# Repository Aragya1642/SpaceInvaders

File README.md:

# Space Invaders Bop-It

The Space Invaders Bop-It is an embedded interactive game that combines the reflex-based mechanics of Bop-It with the space-themed gameplay of Space Invaders. Built around the ATMega328P microcontroller, this project incorporates physical controls, audio/visual feedback, and a custom PCB to deliver an engaging and fast-paced user experience.

## Overview

Players are prompted with random commands such as:

- Turn Left
- Turn Right
- Throttle Up
- Shoot

Each command corresponds to one of the three physical inputs:
- Steering Wheel
- Throttle Lever
- Push Button

Correct responses increase the player’s score, flash a green LED, and play a "ding" sound. Incorrect or delayed responses trigger a red LED, a crash sound, and reset the game. The objective is to reach a score of 99 without failure.

## Features

- Three unique analog/digital inputs: steering, throttle, fire
- LCD screen to display real-time score
- DFPlayer Mini for audio feedback via speakers
- LED indicators for success and failure
- Finite State Machine logic with decreasing response time per successful input
- Enclosure design using Onshape CAD and laser-cut acrylic
- Custom PCB built in KiCad with support for power regulation, audio, and I/O

## Repository Structure

├── src/ # Arduino software

├── pcb/ # KiCad PCB design files

├── cad/ # CAD screenshots and Onshape link

├── docs/ # Final report and additional documentation

├── media/ # Photos and video demonstration

├── LICENSE

└── README.md

## How to Build

1. Clone this repository:
https://github.com/iamratedpg13/SpaceInvaders.git

2. Upload `src/main.ino` to an ATMega328P or Arduino Uno-compatible board.

3. Assemble the PCB using the files in the `pcb/` directory.

4. 3D print or laser cut enclosure parts using the files or images in `cad/`.

5. Copy required `.mp3` sound files to a FAT32-formatted microSD card and insert it into the DFPlayer Mini module.

6. Power the system using a regulated 5V supply (e.g., 9V battery with onboard regulator).

## Video Demo

Watch the game in action:  
https://www.youtube.com/watch?v=FF51uR-_Np4

## Key Implementation Notes

- The throttle and wheel are analog inputs (potentiometers); the button is digital.
- AVCC on the ATMega must be tied to 5V for proper ADC operation.
- Sound and display use UART and I2C, respectively; serial conflicts were resolved manually.
- Input drift was corrected in software by sampling baseline values at startup.

## Team Members

- PJ Granieri – Hardware and PCB Design
- Joshua Krymgold – Software Development
- Aragya Goyal – Enclosure Design and CAD

## License

This project is licensed under the MIT License. See the LICENSE file for details.

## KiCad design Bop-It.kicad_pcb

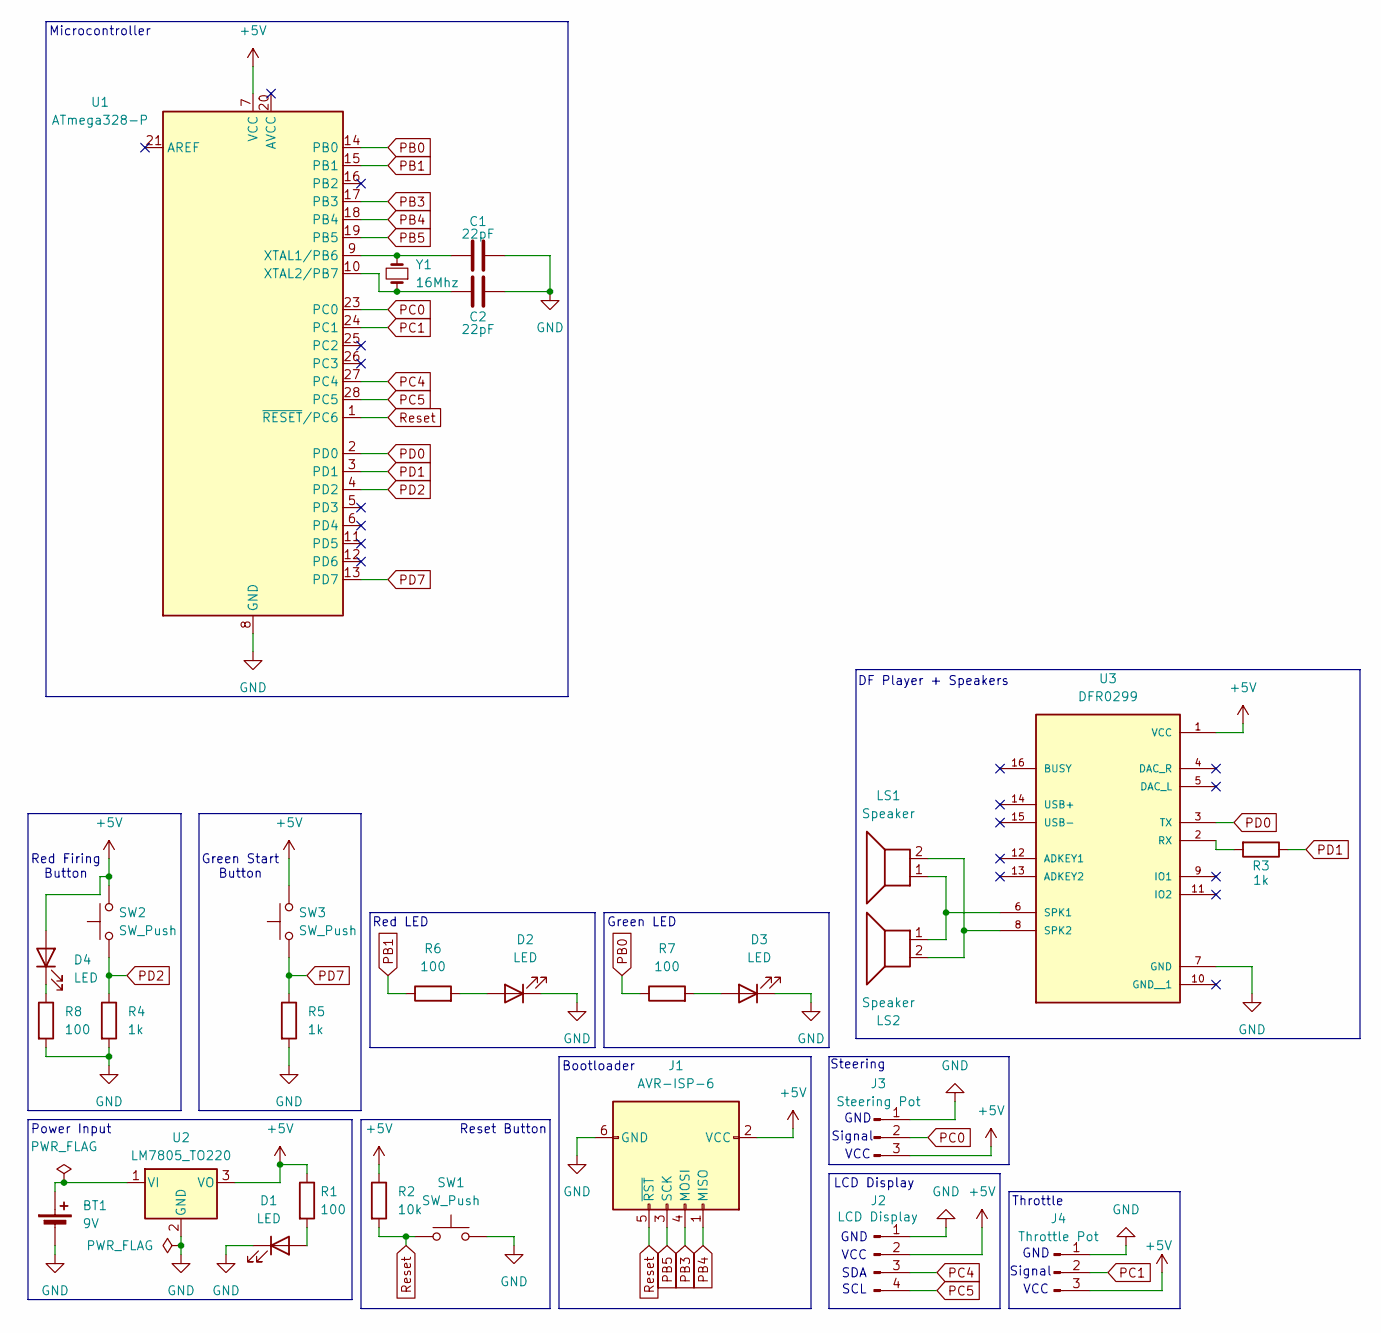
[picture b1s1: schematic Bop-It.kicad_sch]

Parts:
BT1: 9V; PinHeader_1x02_P2.54mm_Vertical
C1, C2: 22pF; C_Disc_D5.0mm_W2.5mm_P5.00mm
D1: LED; LED_D5.0mm
D2, D3, D4: LED; PinHeader_1x02_P2.54mm_Vertical
J1: AVR-ISP-6; PinHeader_2x03_P2.54mm_Vertical
J2: LCD Display; PinHeader_1x04_P2.54mm_Vertical
J3: Steering Pot; PinHeader_1x03_P2.54mm_Vertical
J4: Throttle Pot; PinHeader_1x03_P2.54mm_Vertical
LS1, LS2: Speaker; PinHeader_1x02_P2.54mm_Vertical
R1, R6, R7, R8: 100; R_Axial_DIN0207_L6.3mm_D2.5mm_P7.62mm_Horizontal
R2: 10k; R_Axial_DIN0207_L6.3mm_D2.5mm_P7.62mm_Horizontal
R3, R4, R5: 1k; R_Axial_DIN0207_L6.3mm_D2.5mm_P7.62mm_Horizontal
SW1: SW_Push; SW_PUSH-12mm
SW2, SW3: SW_Push; PinHeader_1x02_P2.54mm_Vertical
U1: ATmega328-P; DIP-28_W7.62mm
U2: LM7805_TO220; TO-220-3_Vertical
U3: DFR0299; MODULE_DFR0299
Y1: 16Mhz; XTAL_HC49P488W46L1150T500H350

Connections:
+5V: D4.2 (A), J1.2 (VCC), J2.2, J3.3, J4.3, R1.1, R2.1, SW2.2, SW3.2, U1.7 (VCC), U2.3 (VO), U3.1 (VCC)
GND: BT1.2 (-), C1.2, C2.2, D1.1 (K), D2.1 (K), D3.1 (K), J1.6 (GND), J2.1, J3.1, J4.1, R4.2, R5.2, R8.2, SW1.2, U1.8 (GND), U1.22 (GND), U2.2 (GND), U3.7 (GND)
unnamed: BT1.1 (+), U2.1 (VI)
unnamed: D1.2 (A), R1.2
unnamed: D2.2 (A), R6.2
unnamed: D3.2 (A), R7.2
unnamed: D4.1 (K), R8.1
unnamed: C1.1, U1.9 (XTAL1/PB6), Y1.2
unnamed: C2.1, U1.10 (XTAL2/PB7), Y1.1
unnamed: R3.2, U3.2 (RX)
unnamed: LS1.1, LS2.1, U3.6 (SPK1)
unnamed: LS1.2, LS2.2, U3.8 (SPK2)
PB0: R7.1, U1.14 (PB0)
PB1: R6.1, U1.15 (PB1)
PB3: J1.4 (MOSI), U1.17 (PB3)
PB4: J1.1 (MISO), U1.18 (PB4)
PB5: J1.3 (SCK), U1.19 (PB5)
PC0: J3.2, U1.23 (PC0)
PC1: J4.2, U1.24 (PC1)
PC4: J2.3, U1.27 (PC4)
PC5: J2.4, U1.28 (PC5)
PD0: U1.2 (PD0), U3.3 (TX)
PD1: R3.1, U1.3 (PD1)
PD2: R4.1, SW2.1, U1.4 (PD2)
PD7: R5.1, SW3.1, U1.13 (PD7)
Reset: J1.5 (~RST), R2.2, SW1.1, U1.1 (~RESET/PC6)

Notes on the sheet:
Steering
VCC
DF Player + Speakers
GND
SDA
Throttle
Signal
Red LED
Reset Button
Bootloader
Power Input
LCD Display
Green LED
SCL
Red Firing Button
Green Start Button
Microcontroller

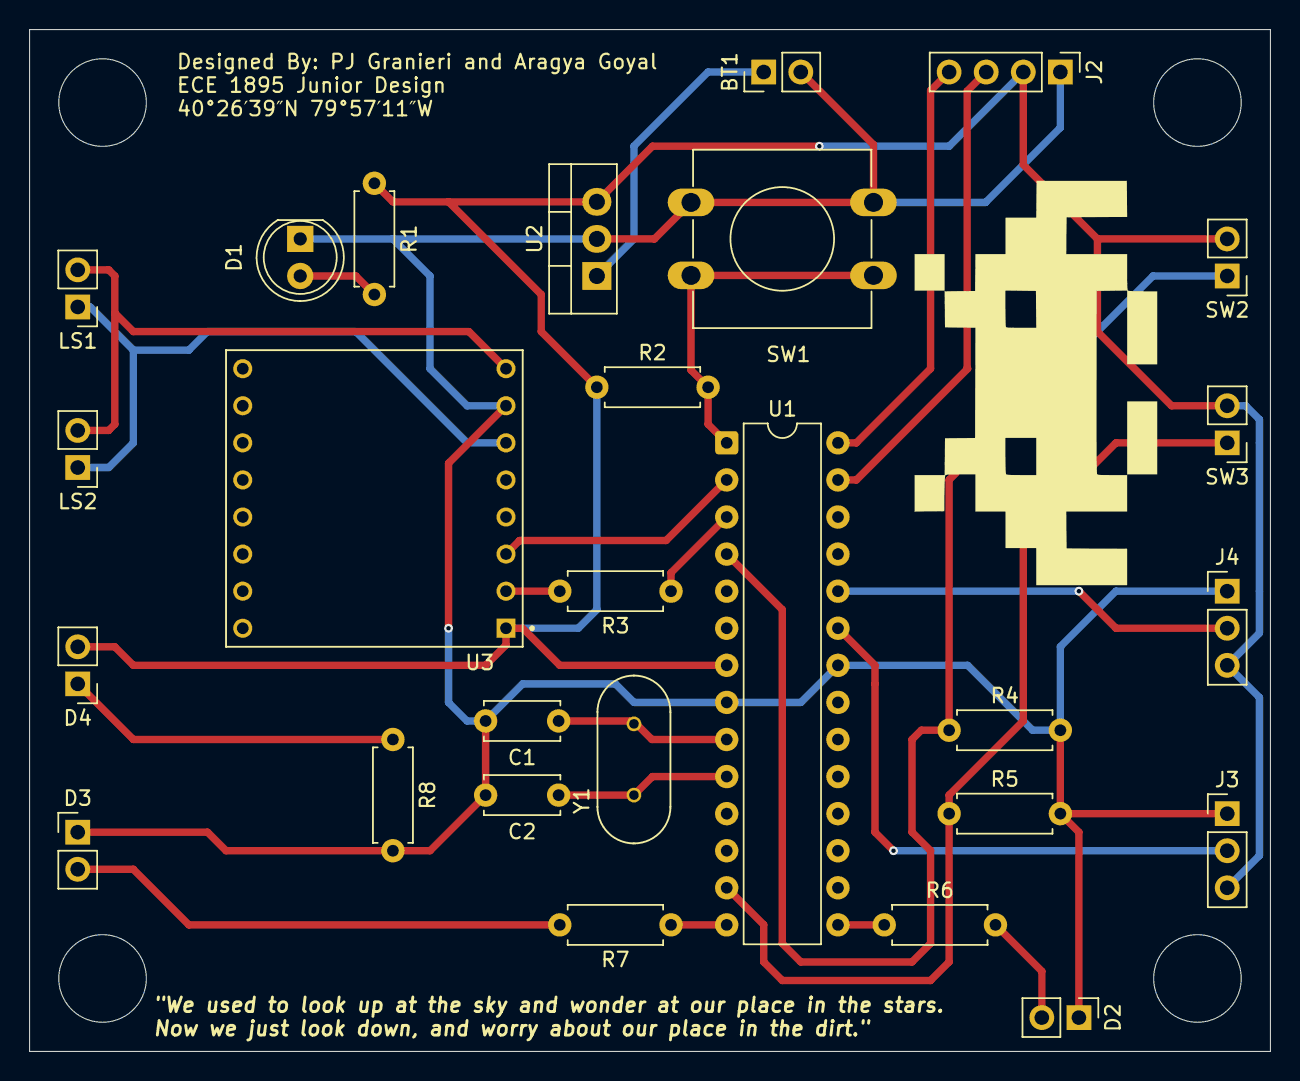
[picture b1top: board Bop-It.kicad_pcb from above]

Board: 2 copper layers, 85.0 x 70.0 mm, 27 parts (0 on the bottom side), 23 nets.

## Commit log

2025-03-18 Uploading Code from Assignment #9
2025-03-18 Update Blink
2025-03-19 Fixed naming
2025-03-19 Removed name for fork
2025-03-19 Added name for fork
2025-03-19 changed name
2025-03-19 Add name as it was forgotten in the PR
2025-03-21 Spaceinvaders PCB design schematic
2025-04-11 Updated PCB Files
2025-05-04 Delete SpaceInvaders.kicad_sch
    Outdated file cleanup
2025-05-04 Delete ~SpaceInvaders.kicad_sch.lck
    Outdated file cleanup
2025-05-04 Delete SpaceInvaders.kicad_pro
    Outdated file cleanup
2025-05-04 Delete SpaceInvaders.kicad_prl
    Outdated file cleanup
2025-05-04 Delete SpaceInvaders.kicad_pcb
    Outdated file cleanup
2025-05-04 Delete Blinkone.ino
    Outdated file cleanup
2025-05-04 Delete #auto_saved_files#
    Outdated file cleanup
2025-05-04 Delete SpaceInvaders-backups directory
    Outdated file cleanup
2025-05-04 Repo clean up
2025-05-04 Repo cleanup
2025-05-04 Design Documents added
2025-05-04 Presentation added
2025-05-04 Create LICENSE
2025-05-04 PCB Photo
2025-05-04 Rename Space_invaders_PCB.jpeg to media/Space_invaders_PCB.jpeg
